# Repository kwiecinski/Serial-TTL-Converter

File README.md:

# Serial-TTL-Converter
 RS232<->TTL converter that is using internal serial port of the PC. Project contain 5V to -12V/+12V converters and all required receivers/transceivers.

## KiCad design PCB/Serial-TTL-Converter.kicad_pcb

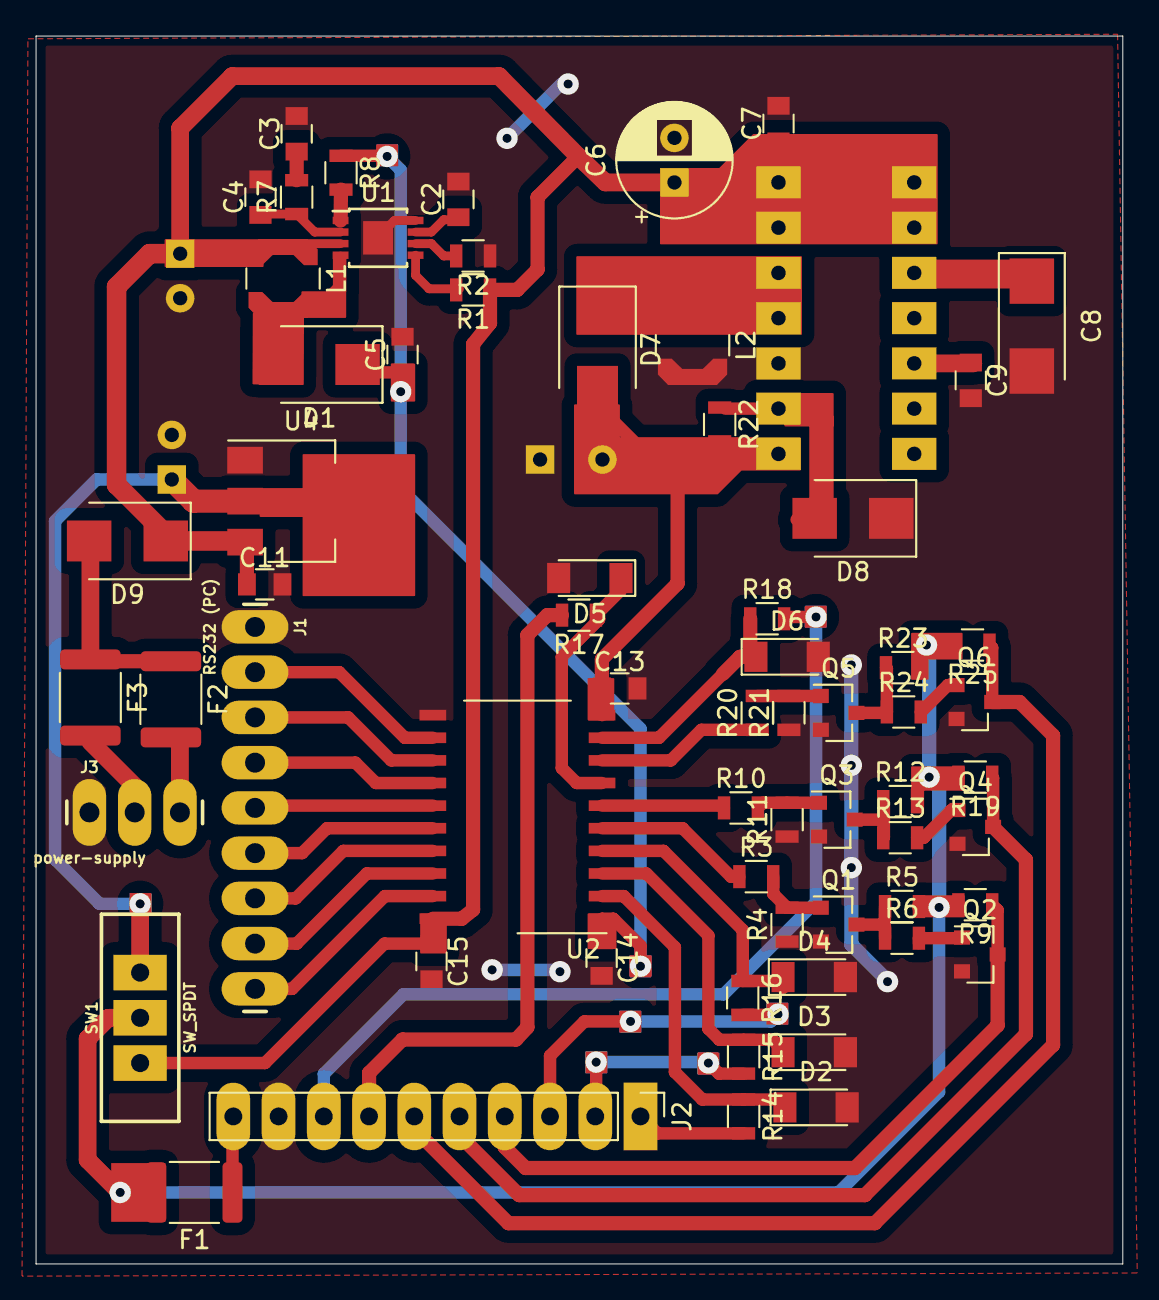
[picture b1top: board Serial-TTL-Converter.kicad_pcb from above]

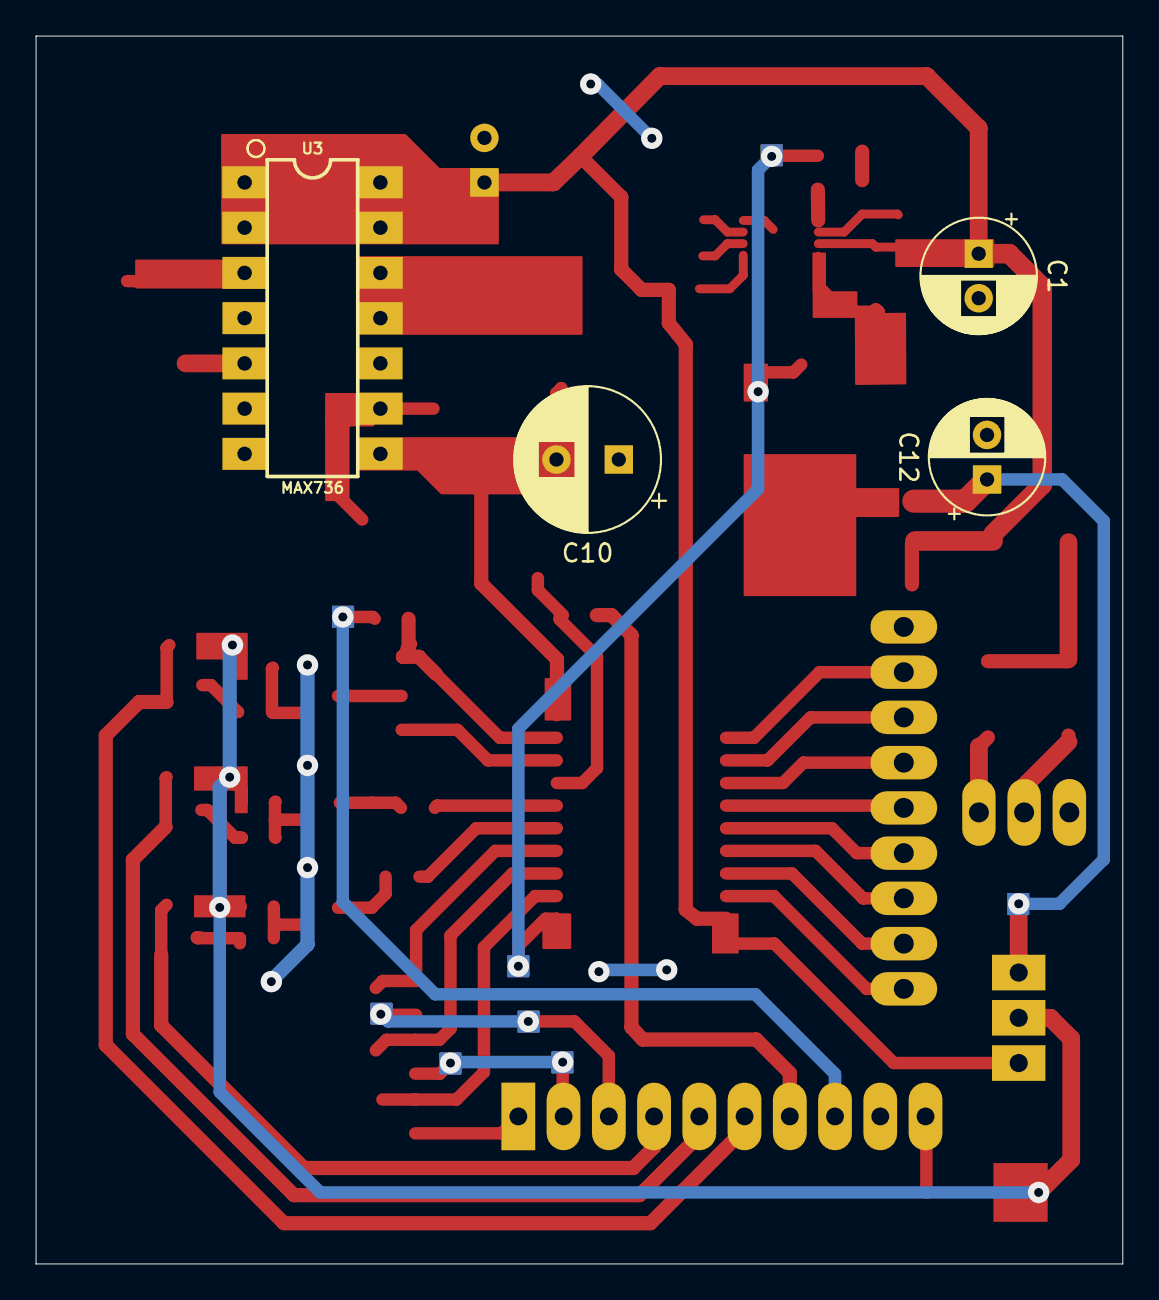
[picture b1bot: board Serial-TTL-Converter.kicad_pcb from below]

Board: 2 copper layers, 61.0 x 68.9 mm, 68 parts (4 on the bottom side), 54 nets.

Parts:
C1, C6, C12: 100u/6V3; CP_Radial_D6.3mm_P2.50mm
C2, C7, C9, C13, C14, C15: 100n; C_0805
C3: 2n2; C_0805
C4: 47p; C_0805
C5: 2u2; C_0805
C8: 22u; CP_Tantalum_Case-C_EIA-6032-28_Reflow
C10: 270u/16V; CP_Radial_D8.0mm_P3.50mm
C11: 1u; C_0805
D1, D7, D8, D9: STPS1L30U; D_SMB
D2, D3, D4, D5, D6: 5V1; D_MiniMELF
F1, F2, F3: 500mA (SD050-16 ECE); Fuse_1812_4532Metric
J1: RS232 (PC); 1X09_LONGPADS
J2: TTL (uC); PinHeader_1x10_P2.54mm_Vertical
J3: power-supply; 1X03_LONGPADS
L1: LPS4018-223 (22uH); L_Coilcraft_LPS4018
L2: LPS4018-103 (10uH); L_Coilcraft_LPS4018
Q1, Q2, Q3, Q4, Q5, Q6: BC817; SOT-23
R1, R4, R5, R11, R12, R21, R22, R23: 10k; R_0805
R2: 56k; R_0805
R3, R10, R20: 4k7; R_0805
R6, R13, R24: 2k2; R_0805
R7: 6.2k; R_0805
R8: 130k; R_0805
R9, R19, R25: 510R; R_0805
R14, R15, R16, R17, R18: 330R; R_0805
SW1: SW_SPDT; SWITCH_SPDT_PTH_11.6X4.0MM
U1: LT8570; MSOP-8-1EP_3x3mm_Pitch0.65mm
U2: ST75185; SO-20_12.8x7.5mm_Pitch1.27mm
U3: MAX736; DIP14
U4: AP1117-33; SOT-223

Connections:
+3V3: C12.1, SW1.1, U4.2
+5V: C1.1, C6.1, C7.1, C11.1, C15.1, D9.1, L1.1, R1.1, SW1.3, U1.3, U2.20, U3.1, U3.2, U3.13, U3.14, U4.3
+12V: C5.1, C14.1, D1.1, R8.1, U2.1
-12V: C10.2, C13.1, D7.2, R22.2, U2.10, U3.8
/CTS: J1.4, U2.14
/CTS_UC: J2.7, R17.2
/DCD: J1.9, U2.19
/DCD_UC: J2.1, R14.2
/DSR: J1.7, U2.17
/DSR_UC: J2.3, R16.2
/DTR: J1.5, U2.15
/DTR_L: R10.1, U2.6
/DTR_UC: J2.5, Q4.3, R19.1
/RI: J1.2, U2.12
/RI_UC: J2.8, R18.2
/RTS: J1.3, U2.13
/RTS_L: R20.1, U2.8
/RTS_UC: J2.6, Q6.3, R25.1
/RX: J1.8, U2.18
/RX_UC: J2.2, R15.2
/TX: J1.6, U2.16
/TX_L: R3.1, U2.5
/TX_UC: J2.4, Q2.3, R9.1
GND: C1.2, C2.2, C3.2, C4.2, C5.2, C6.2, C7.2, C8.2, C9.2, C10.1, C11.2, C12.2, C13.2, C14.2, C15.2, D2.2, D3.2, D4.2, D5.2, D6.2, D8.1, J1.1, J2.9, J3.1, L2.2, Q1.2, Q2.2, Q3.2, Q4.2, Q5.2, Q6.2, R2.1, R4.1, R11.1, R21.1, U1.8, U1.9, U2.11, U3.10, U4.1
unnamed: C2.1, U1.7
unnamed: C3.1, R7.2
unnamed: C4.1, R7.1, U1.2
unnamed: C8.1, U3.3
unnamed: C9.1, U3.5
unnamed: D1.2, L1.2, U1.4
unnamed: D2.1, R14.1, U2.2
unnamed: D3.1, R15.1, U2.3
unnamed: D4.1, R16.1, U2.4
unnamed: D5.1, R17.1, U2.7
unnamed: D6.1, R18.1, U2.9
unnamed: D7.1, L2.1, U3.11, U3.12
unnamed: D8.2, R22.1, U3.9
unnamed: D9.2, F2.1, F3.1
unnamed: F1.1, J2.10
unnamed: F2.2, J3.3
unnamed: F3.2, J3.2
unnamed: Q1.1, R3.2, R4.2
unnamed: Q1.3, R5.1, R6.1
unnamed: Q2.1, R6.2
unnamed: Q3.1, R10.2, R11.2
unnamed: Q3.3, R12.1, R13.1
unnamed: Q4.1, R13.2
unnamed: Q5.1, R20.2, R21.2
unnamed: Q5.3, R23.1, R24.1
unnamed: Q6.1, R24.2
unnamed: R1.2, U1.5
unnamed: R2.2, U1.6
unnamed: R8.2, U1.1
VCC: F1.2, R5.2, R9.2, R12.2, R19.2, R23.2, R25.2, SW1.2

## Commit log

2020-07-28 doc, pcb first upload
2020-08-04 Schematic update
2020-08-06 Add footprints, remove TTL inputs transistors, add 3V3 supply
2020-08-19 library add
2020-08-19 Footprints update, PCB routing
2020-08-19 Capacitor footprint change
2020-08-20 PCB routing
2020-09-02 Resizing pads
2021-01-22 Major concept change - use MAX2323 istead of ST75185 (no need power converters)
